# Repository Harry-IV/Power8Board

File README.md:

# Power8Board V1

48V → 12V Power Distribution & Current-Sensing Board for 8 Thrusters

## Overview

Power8Board is a custom power distribution and sensing PCB intended for robotics applications (e.g. ROVs / AUVs) where 6 DoF control is needed from eight thrusters. 

The board converts 48V DC into 5V and 12V rails, distributes power to eight ESCs, and provides per-thruster current measurement and voltage rail monitoring (3.3, 5, 12, 48) over I²C.

---

## Power Architecture

Two [MPQ860-12V72-L48NBMC](https://www.digikey.com/en/products/detail/murata-power-solutions-inc/MPQ860-12V72-L48NBMC/26005878?s=N4IgTCBcDaILYAcCOAOAbABhAXQL5A) 860W power converters are used to step down 48 to 12V with high efficiency. This 12V power is then routed to eight XT30U-M connectors which ESCs can then connect to for power. These were chosen due to having four power pins, allowing for better heat distribution, and for their active current sharing capabilities. With ~1500W (not 1720 due to drop in max wattage output when current sharing), eight standard T200 thrusters can be driven at full power. This 12V can also be used to power other 12V devices using the [MR30 connector](https://www.tme.com/us/en-us/details/mr30pw-m/dc-power-connectors/amass/) on the board. 

Additionally, a [UWS-5/10-Q48N-C](https://www.digikey.com/en/products/detail/murata-power-solutions-inc/UWS-5-10-Q48N-C/3041704?s=N4IgTCBcDaIKoHUDKBaArAegIwAYUEUAWADgDkUBhEAXQF8g) 100W power converter is used to step down 48V to 5V. This 5V is outputted through the MR30 and can be used to power a Raspberry Pi for instance.

---

## Current Sensing

Monitor thruster load and detect abnormal conditions (e.g. over-current):

### Current-Sense Amplifiers
  * [INA240A2](https://www.ti.com/product/INA240) (analog)
  * One per ESC channel
  * 50x amplification value (50V/V gain)
* 0.0033 $\Omega$ shunt resistor placed in series with each 12V output
  * Scale factor: 1 / (SHUNT_VALUE * AMP_FACTOR) = 1 / (0.0033 * 50) = 6.061
  * current = 6.061 * (output of INA240)
* Analog output routed to ADC inputs with RC-filter (680 $\Omega$, 2.2 uF)

### Channel Organization

* Left side: 4 thrusters
* Right side: 4 thrusters
* Each side feeds into its own ADC, an [ADS1015](https://www.ti.com/product/ADS1015) (12-bit, I²C interfacing)
* I²C address:
  * Left: 0x48
  * Right: 0x49

---

## Voltage Sensing

Monitor that voltage rails are within normal bounds.

### Power Rails

| Rail  | Purpose                    |
| ----- | -------------------------- |
| 48 V  | Main input power           |
| 12 V  | ESC & thruster power       |
| 5 V   | Miscellaneous              |
| 3.3 V | ADCs, current sensors, I²C |

### ADC

* [ADS1015](https://www.ti.com/product/ADS1015) (12-bit, I²C interfacing)
  * Used for measuring the voltages
  * Address: 0x4A

### Voltage Dividers

### Scalar Values
  * 48V: (470+25)/25 = 19.8
  * 12V: (470+110)/110 = 5.273
  * 5V: (470+470)/470 = 2
  * 3.3V: (470+470)/470 = 2

Multiply these values read from the ADC by these scalars respectively to find their true voltages.

---

## LED Indicators

| Rail  | Color                      |
| ----- | -------------------------- |
| 48 V  | Green                      |
| 12 V  | Yellow                     |
| 5 V   | Red                        |
| 3.3 V | Amber                      |

---

## PCB Layout

### 6-layer stackup

| Layer | Type                      |
| ----- | ------------------------- |
| 1     | Signal                    |
| 2     | Ground                    |
| 3     | Signal - Power (3.3V)     |
| 4     | Power (12V & 48V)         |
| 5     | Ground                    |
| 6     | Signal                    |

### Design notes

* Nearly all analog traces are routed on layer 3 to reduce effects of digital noise.
* Copper pours help with thermal dissipation.
* Via-in-pad is used to condense routing. It's also a standard option for 6-layer boards when ordering with JLCPCB.
* Ground on layer 2 & 5 provides low-impedance return path and reduce EMI.
* Power converters connect from the backside. 

---

## Ordering

To order, navigate to Power8Board V1/Export. Use Power8Board V1.zip for ordering the PCB and Power8Board V1 Stencil.zip for ordering a stencil (very helpful for soldering). Here are the options I chose when ordering from JLCPCB:

For ordering the components, navigate to Power8Board V1/bom and click on ibom.html. This BOM is interactive, making it great for ordering and knowing where components go while soldering. **Note that this does not include all components for making the board.** This is because pin receptacles are soldered onto the pads for all power converters. Here are the two types of pin receptacles used on the board:

Pin #1: https://www.digikey.com/en/products/detail/mill-max-manufacturing-corp/0372-0-15-15-13-27-10-0/433860

Pin #2: https://www.digikey.com/en/products/detail/mill-max-manufacturing-corp/0312-0-15-15-34-27-10-0/433567

Pin #1 is used on pads 4, 5, 7, and 8 on both 48V-12V converters and on pads 4 and 8 on the 48V-5V converter (10 in total)

Pin #2 is used on pads 1, 2, and 3 on both 48V-12V converters and on pads 1, 2, 3, 5, 6, and 7 on the 48V-5V converter (12 in total)

---

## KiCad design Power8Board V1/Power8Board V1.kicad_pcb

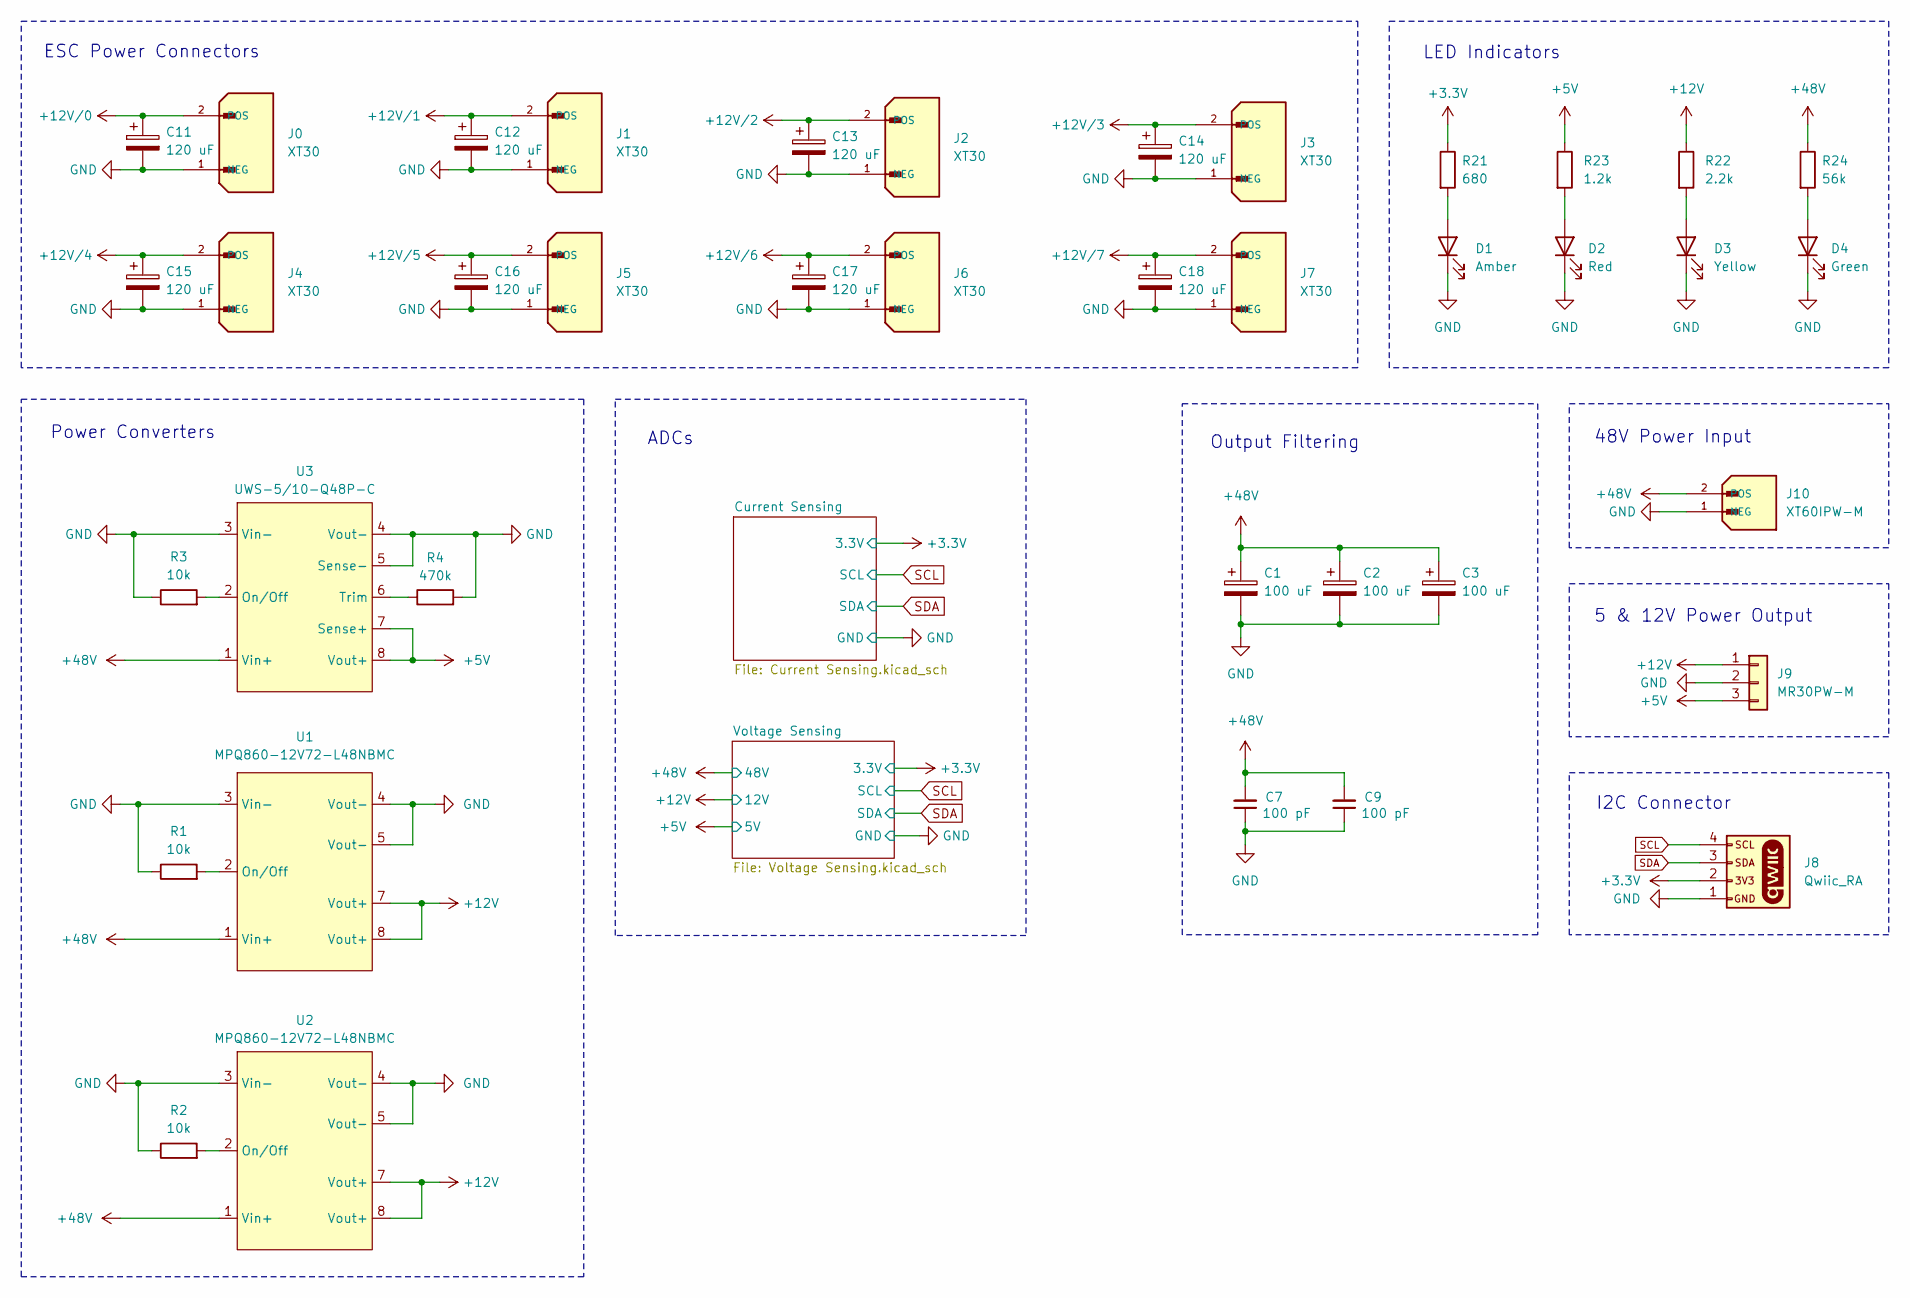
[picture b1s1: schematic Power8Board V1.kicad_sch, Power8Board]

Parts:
C1, C2, C3: 100 uF; CAP_AVG-8x12_ILC; Part # 107AVG063MFBJ
C7, C9: 100 pF; CAPC2012X140N; Part # KGQ21HCG2A101JT
C11, C12, C13, C14, C15, C16, C17, C18: 120 uF; PCAP_SVP_C6_PAN-M; Part # 20SVPF120M
D1: Amber; WL-SMCW_0805; Part # 150080AS75000
D2: Red; WL-SMCW_0805; Part # 150080RS75000
D3: Yellow; WL-SMCW_0805; Part # 150080YS75000
D4: Green; WL-SMCW_0805; Part # 150080GS75000
J0, J1, J2, J3, J4, J5, J6, J7: XT30; AMASS_XT30U-M_1x02_P5.0mm_Vertical; Part # XT30U-M
J8: Qwiic_RA; QWIIC Connector RA; Part # SM04B-SRSS-TB
J9: MR30PW-M; AMASS_MR30PW-M_1x03_P3.50mm_Horizontal; Part # MR30PW-M
J10: XT60IPW-M; AMASS_XT60IPW-M_1x03_P7.20mm_Horizontal; Part # XT60IPW-M
R1, R2, R3: 10k; R_0805_2012Metric; Part # CRGCQ0805F10K
R4: 470k; R_0805_2012Metric; Part # CRGCQ0805F470K
R21: 680; R_0805_2012Metric; Part # CRGCQ0805F680R
R22: 2.2k; R_0805_2012Metric; Part # CRGCQ0805F2K2
R23: 1.2k; R_0805_2012Metric; Part # CRGCQ0805F1K2
R24: 56k; R_0805_2012Metric; Part # CRGCQ0805F56K
U1, U2: MPQ860-12V72-L48NBMC; Part # MPQ860-12V72-L48NBMC
U3: UWS-5_10-Q48; Part # UWS-5/10-Q48P-C

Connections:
+3.3V: J8.2, R21.1; also elsewhere on the board
+5V: J9.3, R23.1, U3.7 (Sense+), U3.8 (Vout+); also elsewhere on the board
+12V: J9.1, R22.1, U1.7 (Vout+), U1.8 (Vout+), U2.7 (Vout+), U2.8 (Vout+); also elsewhere on the board
+12V/0: C11.1, J0.2 (POS); also elsewhere on the board
+12V/1: C12.1, J1.2 (POS); also elsewhere on the board
+12V/2: C13.1, J2.2 (POS); also elsewhere on the board
+12V/3: C14.1, J3.2 (POS); also elsewhere on the board
+12V/4: C15.1, J4.2 (POS); also elsewhere on the board
+12V/5: C16.1, J5.2 (POS); also elsewhere on the board
+12V/6: C17.1, J6.2 (POS); also elsewhere on the board
+12V/7: C18.1, J7.2 (POS); also elsewhere on the board
+48V: C1.1, C2.1, C3.1, C7.2, C9.2, J10.2 (POS), R24.1, U1.1 (Vin+), U2.1 (Vin+), U3.1 (Vin+); also elsewhere on the board
GND: C1.2, C2.2, C3.2, C7.1, C9.1, C11.2, C12.2, C13.2, C14.2, C15.2, C16.2, C17.2, C18.2, D1.1 (K), D2.1 (K), D3.1 (K), D4.1 (K), J0.1 (NEG), J1.1 (NEG), J2.1 (NEG), J3.1 (NEG), J4.1 (NEG), J5.1 (NEG), J6.1 (NEG), J7.1 (NEG), J8.1, J9.2, J10.1 (NEG), R1.1, R2.1, R3.1, R4.2, U1.3 (Vin-), U1.4 (Vout-), U1.5 (Vout-), U2.3 (Vin-), U2.4 (Vout-), U2.5 (Vout-), U3.3 (Vin-), U3.4 (Vout-), U3.5 (Sense-); also elsewhere on the board
unnamed: D1.2 (A), R21.2
unnamed: D2.2 (A), R23.2
unnamed: D3.2 (A), R22.2
unnamed: D4.2 (A), R24.2
unnamed: R1.2, U1.2 (On/Off)
unnamed: R2.2, U2.2 (On/Off)
unnamed: R3.2, U3.2 (On/Off)
unnamed: R4.1, U3.6 (Trim)
SCL: J8.4; also elsewhere on the board
SDA: J8.3; also elsewhere on the board

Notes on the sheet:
I2C Connector
LED Indicators
48V Power Input
ADCs
Power Converters
Output Filtering
5 & 12V Power Output
ESC Power Connectors

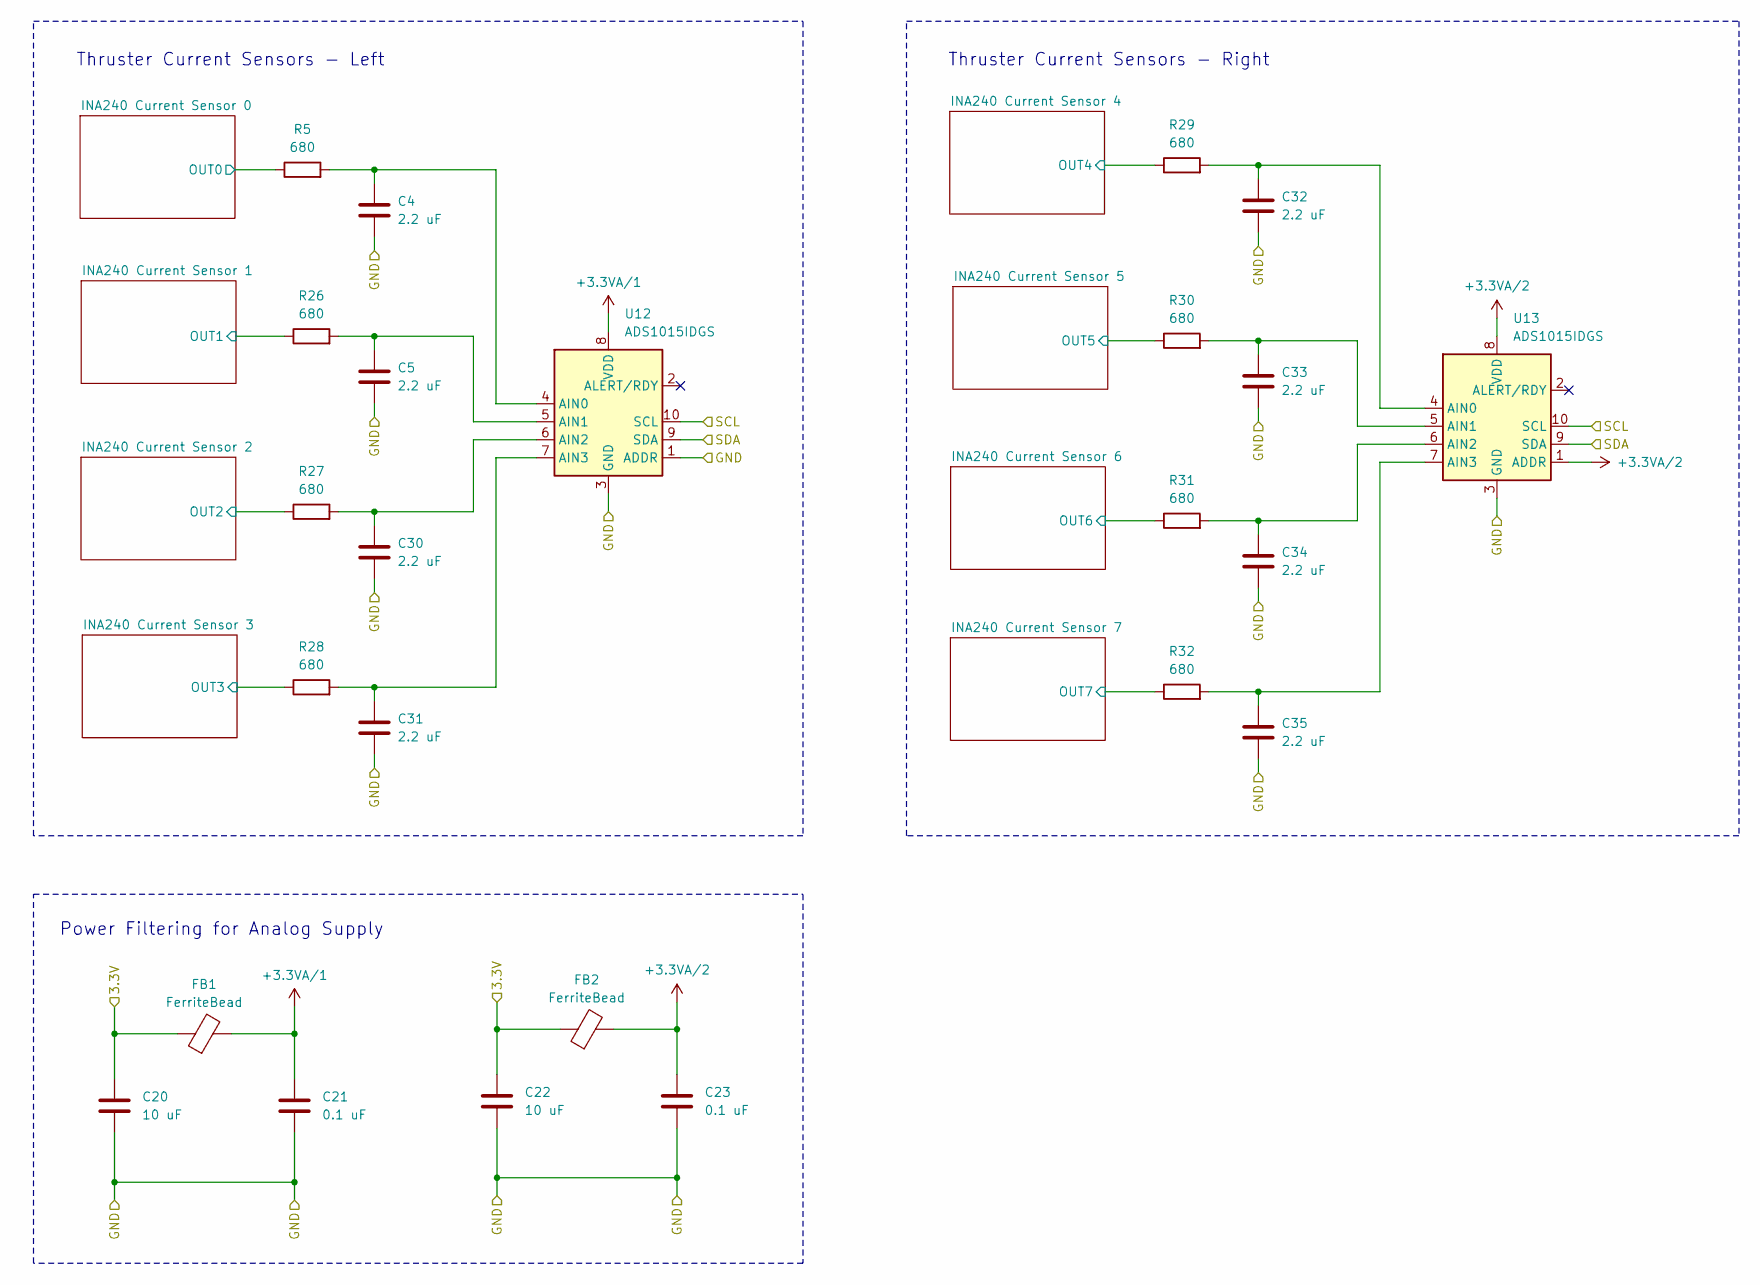
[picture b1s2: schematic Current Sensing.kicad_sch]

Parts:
C4, C5, C30, C31, C32, C33, C34, C35: 2.2 uF; C_0603_1608Metric; Part # GRM188Z71E225KE43D
C20, C22: 10 uF; C_0603_1608Metric; Part # GRM188R61E106KA73D
C21, C23: 0.1 uF; C_0603_1608Metric; Part # C0603C104K5RACTU
FB1, FB2: FerriteBead; 0603 Ferrite Bead; Part # BLM18KG102SZ1D
R5, R26, R27, R28, R29, R30, R31, R32: 680; R_0603_1608Metric; Part # CRGCQ0603F680R
U12, U13: ADS1015IDGS; TSSOP-10_3x3mm_P0.5mm; Part # ADS1015IDGSR

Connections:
+3.3V: C20.1, C22.1, FB1.1, FB2.1; also elsewhere on the board
+3.3VA/1: C21.1, FB1.2, U12.8 (VDD)
+3.3VA/2: C23.1, FB2.2, U13.1 (ADDR), U13.8 (VDD)
/Current Sensing/INA240 Current Sensor 0/OUT0: R5.1; also elsewhere on the board
/Current Sensing/INA240 Current Sensor 1/OUT1: R26.1; also elsewhere on the board
/Current Sensing/INA240 Current Sensor 2/OUT2: R27.1; also elsewhere on the board
/Current Sensing/INA240 Current Sensor 3/OUT3: R28.1; also elsewhere on the board
/Current Sensing/INA240 Current Sensor 4/OUT4: R29.1; also elsewhere on the board
/Current Sensing/INA240 Current Sensor 5/OUT5: R30.1; also elsewhere on the board
/Current Sensing/INA240 Current Sensor 6/OUT6: R31.1; also elsewhere on the board
/Current Sensing/INA240 Current Sensor 7/OUT7: R32.1; also elsewhere on the board
GND: C4.2, C5.2, C20.2, C21.2, C22.2, C23.2, C30.2, C31.2, C32.2, C33.2, C34.2, C35.2, U12.1 (ADDR), U12.3 (GND), U13.3 (GND); also elsewhere on the board
unnamed: C4.1, R5.2, U12.4 (AIN0)
unnamed: C5.1, R26.2, U12.5 (AIN1)
unnamed: C30.1, R27.2, U12.6 (AIN2)
unnamed: C31.1, R28.2, U12.7 (AIN3)
unnamed: C32.1, R29.2, U13.4 (AIN0)
unnamed: C33.1, R30.2, U13.5 (AIN1)
unnamed: C34.1, R31.2, U13.6 (AIN2)
unnamed: C35.1, R32.2, U13.7 (AIN3)
SCL: U12.10 (SCL), U13.10 (SCL); also elsewhere on the board
SDA: U12.9 (SDA), U13.9 (SDA); also elsewhere on the board

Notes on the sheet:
Thruster Current Sensors - Right
Power Filtering for Analog Supply
Thruster Current Sensors - Left

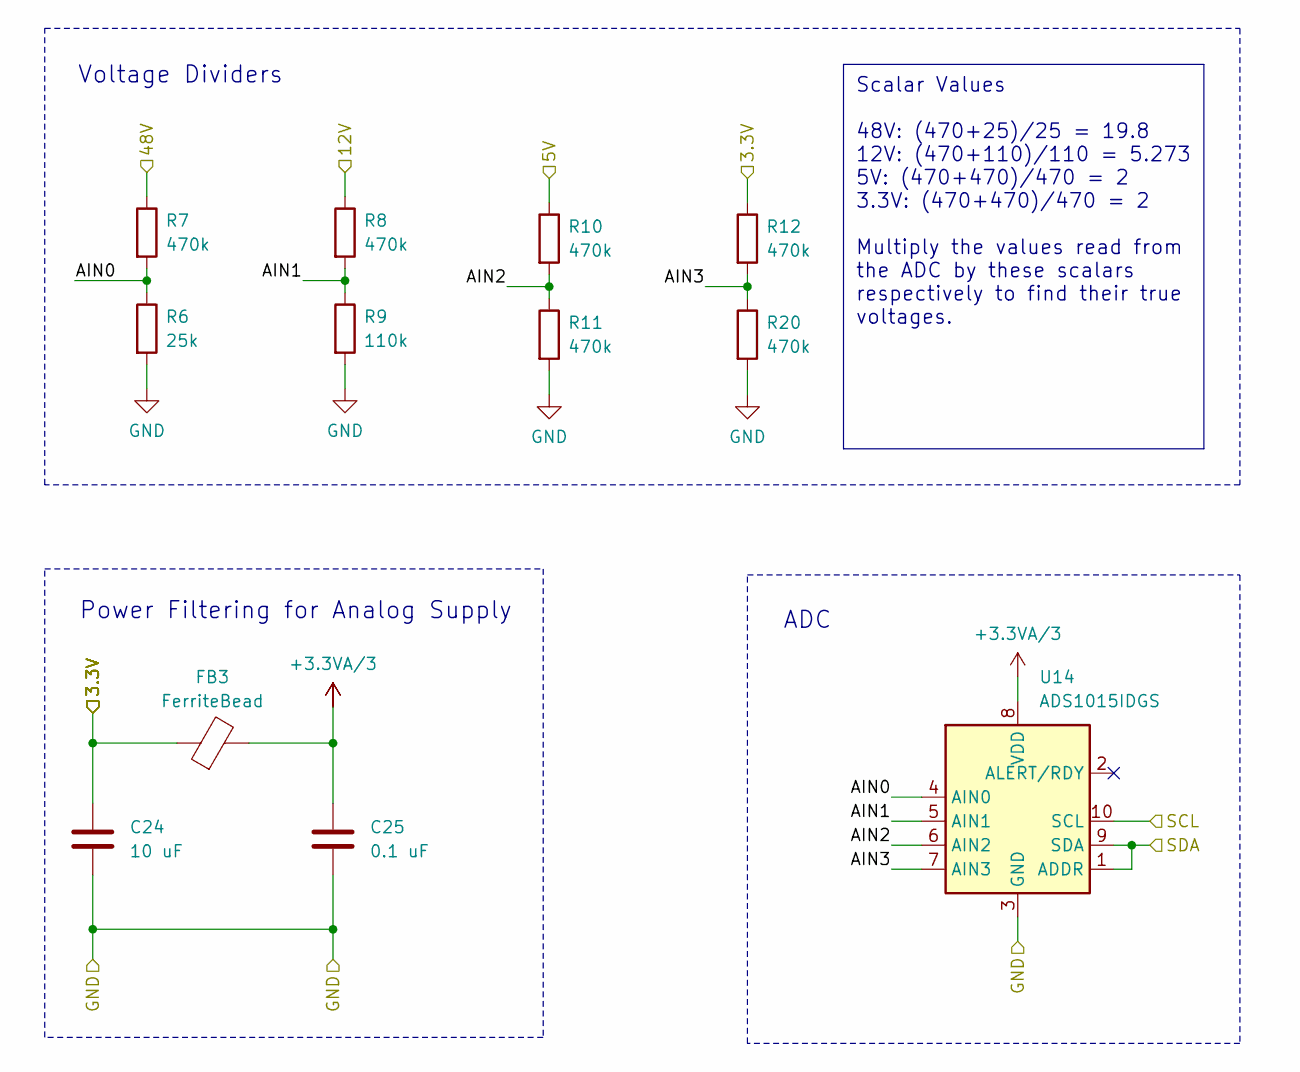
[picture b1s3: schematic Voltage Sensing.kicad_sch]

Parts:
C24: 10 uF; C_0805_2012Metric; Part # GRT21BC71E106KE13L
C25: 0.1 uF; C_0805_2012Metric; Part # C0805C104J5RACAUTO
FB3: FerriteBead; BEADC2012X105N; Part # MPZ2012S102ATD25
R6: 25k; R_0805_2012Metric; Part # CPF-A-0805B25KE
R7, R8, R10, R11, R12, R20: 470k; RES_TNPW0805_VIS; Part # TNPW0805470KBEEA
R9: 110k; R_0805_2012Metric; Part # RQ73C2A110KBTDF
U14: ADS1015IDGS; TSSOP-10_3x3mm_P0.5mm; Part # ADS1015IDGSR

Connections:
+3.3V: C24.1, FB3.1, R12.1; also elsewhere on the board
+3.3VA/3: C25.1, FB3.2, U14.8 (VDD)
+5V: R10.1; also elsewhere on the board
+12V: R8.1; also elsewhere on the board
+48V: R7.1; also elsewhere on the board
/Voltage Sensing/AIN0: R6.1, R7.2, U14.4 (AIN0)
/Voltage Sensing/AIN1: R8.2, R9.1, U14.5 (AIN1)
/Voltage Sensing/AIN2: R10.2, R11.1, U14.6 (AIN2)
/Voltage Sensing/AIN3: R12.2, R20.1, U14.7 (AIN3)
GND: C24.2, C25.2, R6.2, R9.2, R11.2, R20.2, U14.3 (GND); also elsewhere on the board
SCL: U14.10 (SCL); also elsewhere on the board
SDA: U14.1 (ADDR), U14.9 (SDA); also elsewhere on the board

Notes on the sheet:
Scalar Values 48V: (470+25)/25 = 19.8 12V: (470+110)/110 = 5.273 5V: (470+470)/470 = 2 3.3V: (470+470)/470 = 2 Multiply the values read from the ADC by these scalars respectively to find their true voltages.
ADC
Power Filtering for Analog Supply
Voltage Dividers

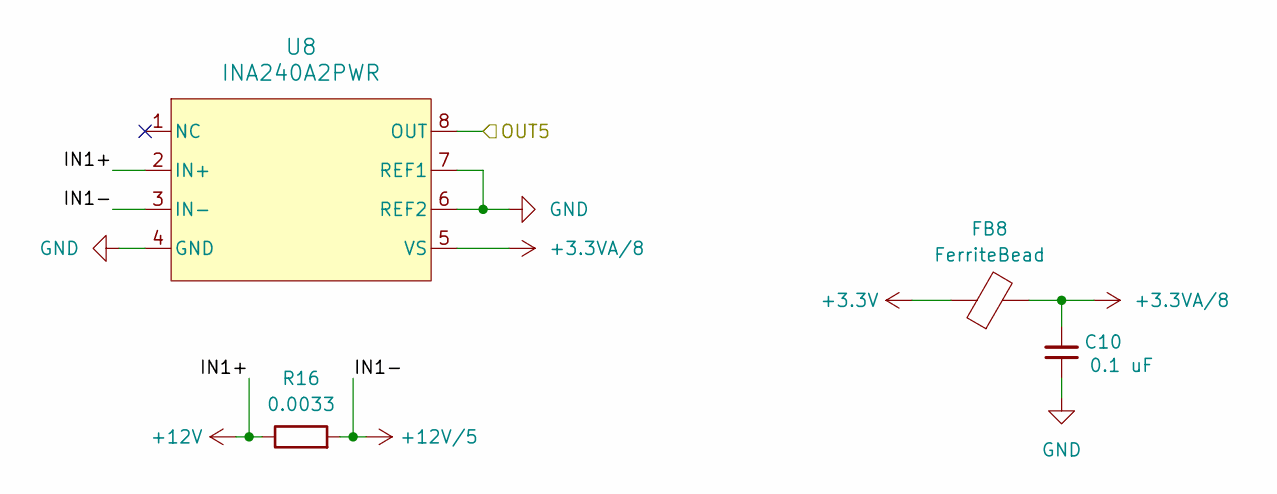
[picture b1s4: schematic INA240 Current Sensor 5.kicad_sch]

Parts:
C10: 0.1 uF; CAPC2012X140N; Part # C0805C104J5RACAUTO
FB8: FerriteBead; BEADC2012X105N; Part # MPZ2012S102ATD25
R16: 0.0033; RES_VISHAY_WSLP2512_A_VIS; Part # WSLP25123L300DEA
U8: INA240A2PWR; PW0008A_M; Part # INA240A2PWR

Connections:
+3.3V: FB8.1; also elsewhere on the board
+3.3VA/8: C10.2, FB8.2, U8.5 (VS)
+12V: R16.1, U8.2 (IN+); also elsewhere on the board
+12V/5: R16.2, U8.3 (IN-); also elsewhere on the board
/Current Sensing/INA240 Current Sensor 5/OUT5: U8.8 (OUT); also elsewhere on the board
GND: C10.1, U8.4 (GND), U8.6 (REF2), U8.7 (REF1); also elsewhere on the board

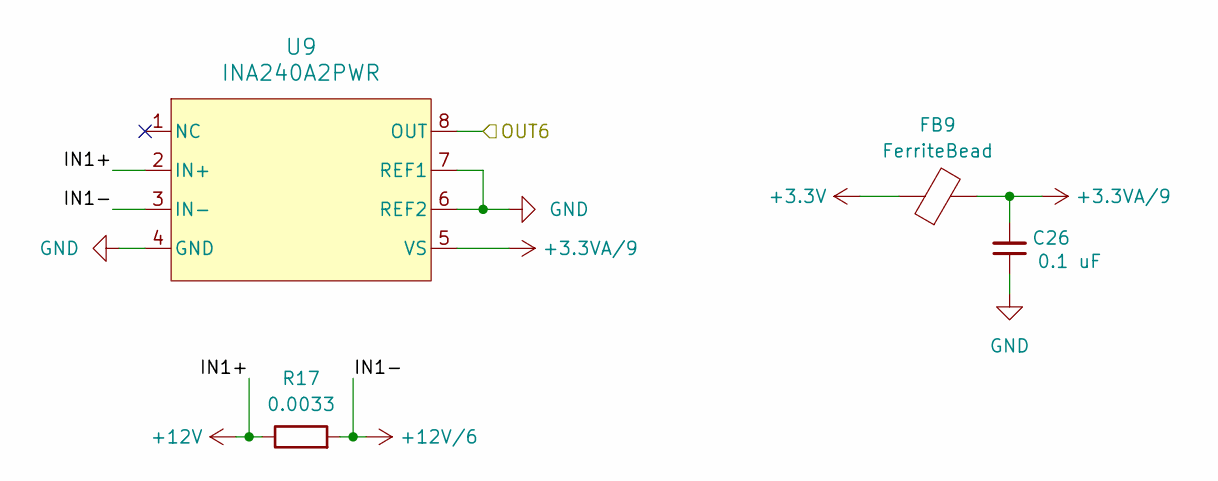
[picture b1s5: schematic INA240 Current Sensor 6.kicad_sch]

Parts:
C26: 0.1 uF; CAPC2012X140N; Part # C0805C104J5RACAUTO
FB9: FerriteBead; BEADC2012X105N; Part # MPZ2012S102ATD25
R17: 0.0033; RES_VISHAY_WSLP2512_A_VIS; Part # WSLP25123L300DEA
U9: INA240A2PWR; PW0008A_M; Part # INA240A2PWR

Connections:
+3.3V: FB9.1; also elsewhere on the board
+3.3VA/9: C26.2, FB9.2, U9.5 (VS)
+12V: R17.1, U9.2 (IN+); also elsewhere on the board
+12V/6: R17.2, U9.3 (IN-); also elsewhere on the board
/Current Sensing/INA240 Current Sensor 6/OUT6: U9.8 (OUT); also elsewhere on the board
GND: C26.1, U9.4 (GND), U9.6 (REF2), U9.7 (REF1); also elsewhere on the board

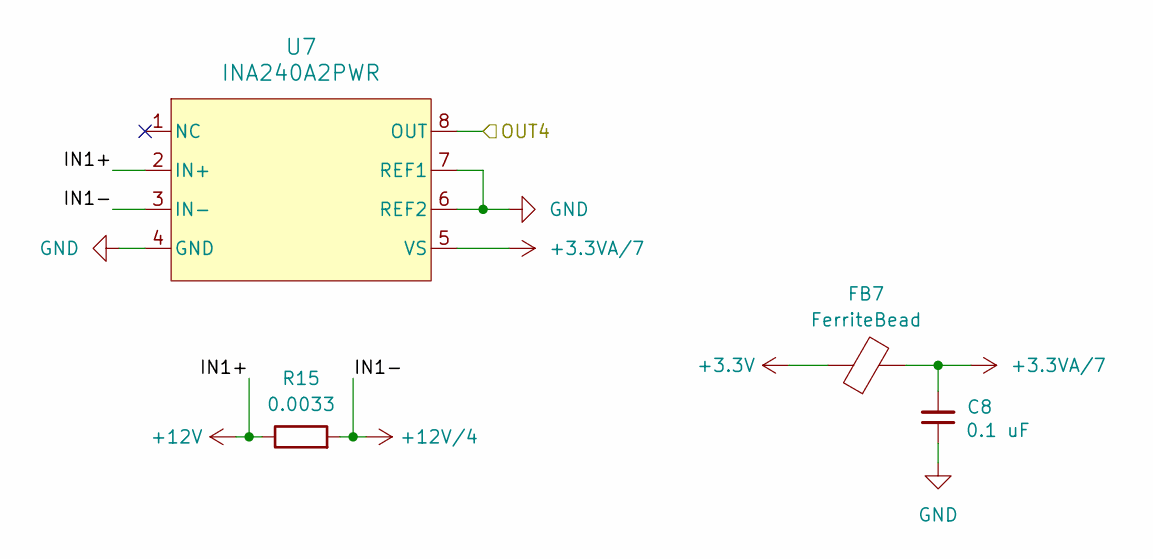
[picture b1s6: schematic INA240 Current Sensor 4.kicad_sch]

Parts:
C8: 0.1 uF; CAPC2012X140N; Part # C0805C104J5RACAUTO
FB7: FerriteBead; BEADC2012X105N; Part # MPZ2012S102ATD25
R15: 0.0033; RES_VISHAY_WSLP2512_A_VIS; Part # WSLP25123L300DEA
U7: INA240A2PWR; PW0008A_M; Part # INA240A2PWR

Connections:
+3.3V: FB7.1; also elsewhere on the board
+3.3VA/7: C8.2, FB7.2, U7.5 (VS)
+12V: R15.1, U7.2 (IN+); also elsewhere on the board
+12V/4: R15.2, U7.3 (IN-); also elsewhere on the board
/Current Sensing/INA240 Current Sensor 4/OUT4: U7.8 (OUT); also elsewhere on the board
GND: C8.1, U7.4 (GND), U7.6 (REF2), U7.7 (REF1); also elsewhere on the board

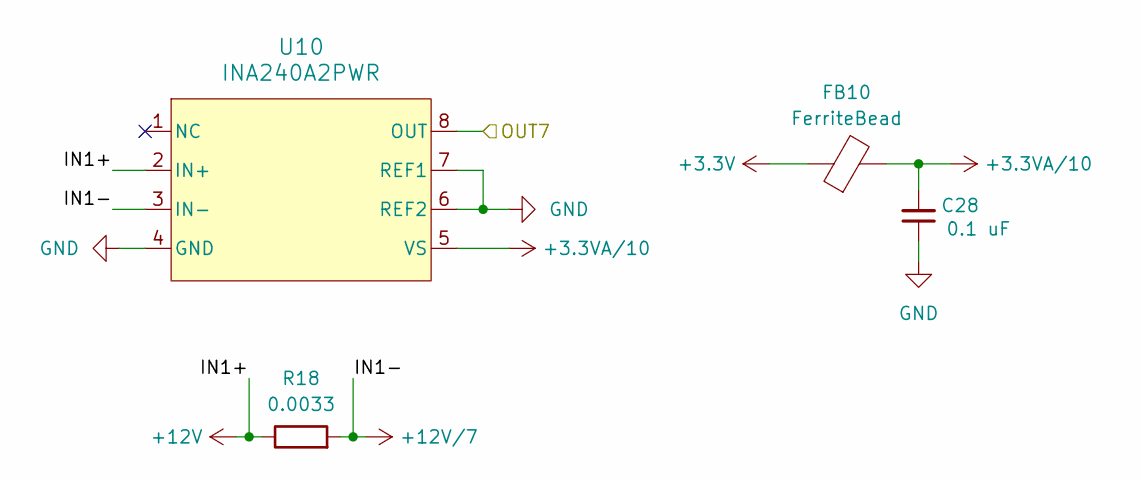
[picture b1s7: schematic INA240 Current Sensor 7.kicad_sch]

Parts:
C28: 0.1 uF; CAPC2012X140N; Part # C0805C104J5RACAUTO
FB10: FerriteBead; BEADC2012X105N; Part # MPZ2012S102ATD25
R18: 0.0033; RES_VISHAY_WSLP2512_A_VIS; Part # WSLP25123L300DEA
U10: INA240A2PWR; PW0008A_M; Part # INA240A2PWR

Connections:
+3.3V: FB10.1; also elsewhere on the board
+3.3VA/10: C28.2, FB10.2, U10.5 (VS)
+12V: R18.1, U10.2 (IN+); also elsewhere on the board
+12V/7: R18.2, U10.3 (IN-); also elsewhere on the board
/Current Sensing/INA240 Current Sensor 7/OUT7: U10.8 (OUT); also elsewhere on the board
GND: C28.1, U10.4 (GND), U10.6 (REF2), U10.7 (REF1); also elsewhere on the board

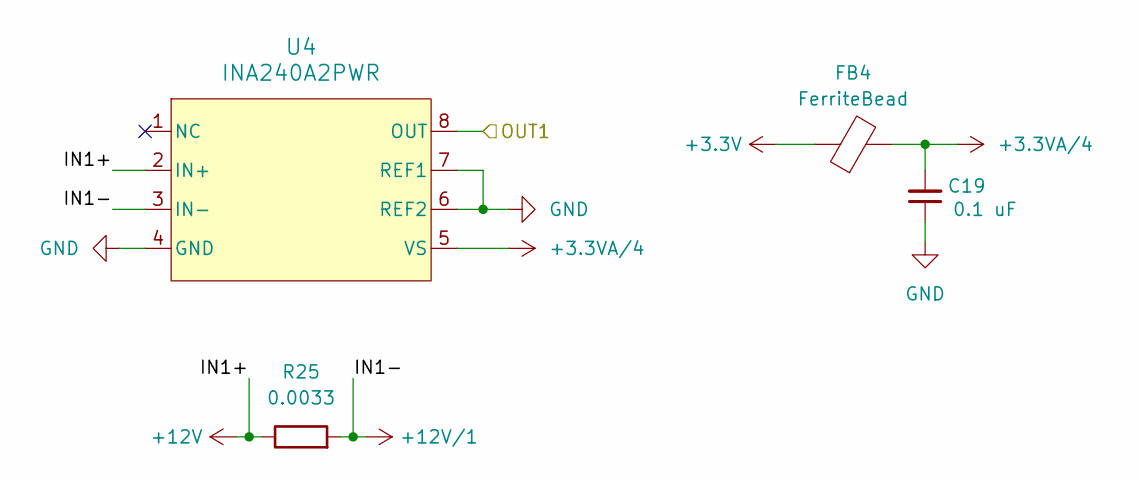
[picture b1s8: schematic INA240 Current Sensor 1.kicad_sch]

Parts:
C19: 0.1 uF; CAPC2012X140N; Part # C0805C104J5RACAUTO
FB4: FerriteBead; BEADC2012X105N; Part # MPZ2012S102ATD25
R25: 0.0033; RES_VISHAY_WSLP2512_A_VIS; Part # WSLP25123L300DEA
U4: INA240A2PWR; PW0008A_M; Part # INA240A2PWR

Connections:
+3.3V: FB4.1; also elsewhere on the board
+3.3VA/4: C19.2, FB4.2, U4.5 (VS)
+12V: R25.1, U4.2 (IN+); also elsewhere on the board
+12V/1: R25.2, U4.3 (IN-); also elsewhere on the board
/Current Sensing/INA240 Current Sensor 1/OUT1: U4.8 (OUT); also elsewhere on the board
GND: C19.1, U4.4 (GND), U4.6 (REF2), U4.7 (REF1); also elsewhere on the board

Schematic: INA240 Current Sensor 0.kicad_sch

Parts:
C29: 0.1 uF; CAPC2012X140N; Part # C0805C104J5RACAUTO
FB11: FerriteBead; BEADC2012X105N; Part # MPZ2012S102ATD25
R19: 0.0033; RES_VISHAY_WSLP2512_A_VIS; Part # WSLP25123L300DEA
U11: INA240A2PWR; PW0008A_M; Part # INA240A2PWR

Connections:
+3.3V: FB11.1; also elsewhere on the board
+3.3VA/11: C29.2, FB11.2, U11.5 (VS)
+12V: R19.1, U11.2 (IN+); also elsewhere on the board
+12V/0: R19.2, U11.3 (IN-); also elsewhere on the board
/Current Sensing/INA240 Current Sensor 0/OUT0: U11.8 (OUT); also elsewhere on the board
GND: C29.1, U11.4 (GND), U11.6 (REF2), U11.7 (REF1); also elsewhere on the board

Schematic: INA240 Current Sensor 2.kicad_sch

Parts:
C27: 0.1 uF; CAPC2012X140N; Part # C0805C104J5RACAUTO
FB5: FerriteBead; BEADC2012X105N; Part # MPZ2012S102ATD25
R13: 0.0033; RES_VISHAY_WSLP2512_A_VIS; Part # WSLP25123L300DEA
U5: INA240A2PWR; PW0008A_M; Part # INA240A2PWR

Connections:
+3.3V: FB5.1; also elsewhere on the board
+3.3VA/5: C27.2, FB5.2, U5.5 (VS)
+12V: R13.1, U5.2 (IN+); also elsewhere on the board
+12V/2: R13.2, U5.3 (IN-); also elsewhere on the board
/Current Sensing/INA240 Current Sensor 2/OUT2: U5.8 (OUT); also elsewhere on the board
GND: C27.1, U5.4 (GND), U5.6 (REF2), U5.7 (REF1); also elsewhere on the board

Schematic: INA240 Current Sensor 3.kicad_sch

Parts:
C6: 0.1 uF; CAPC2012X140N; Part # C0805C104J5RACAUTO
FB6: FerriteBead; BEADC2012X105N; Part # MPZ2012S102ATD25
R14: 0.0033; RES_VISHAY_WSLP2512_A_VIS; Part # WSLP25123L300DEA
U6: INA240A2PWR; PW0008A_M; Part # INA240A2PWR

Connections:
+3.3V: FB6.1; also elsewhere on the board
+3.3VA/6: C6.2, FB6.2, U6.5 (VS)
+12V: R14.1, U6.2 (IN+); also elsewhere on the board
+12V/3: R14.2, U6.3 (IN-); also elsewhere on the board
/Current Sensing/INA240 Current Sensor 3/OUT3: U6.8 (OUT); also elsewhere on the board
GND: C6.1, U6.4 (GND), U6.6 (REF2), U6.7 (REF1); also elsewhere on the board

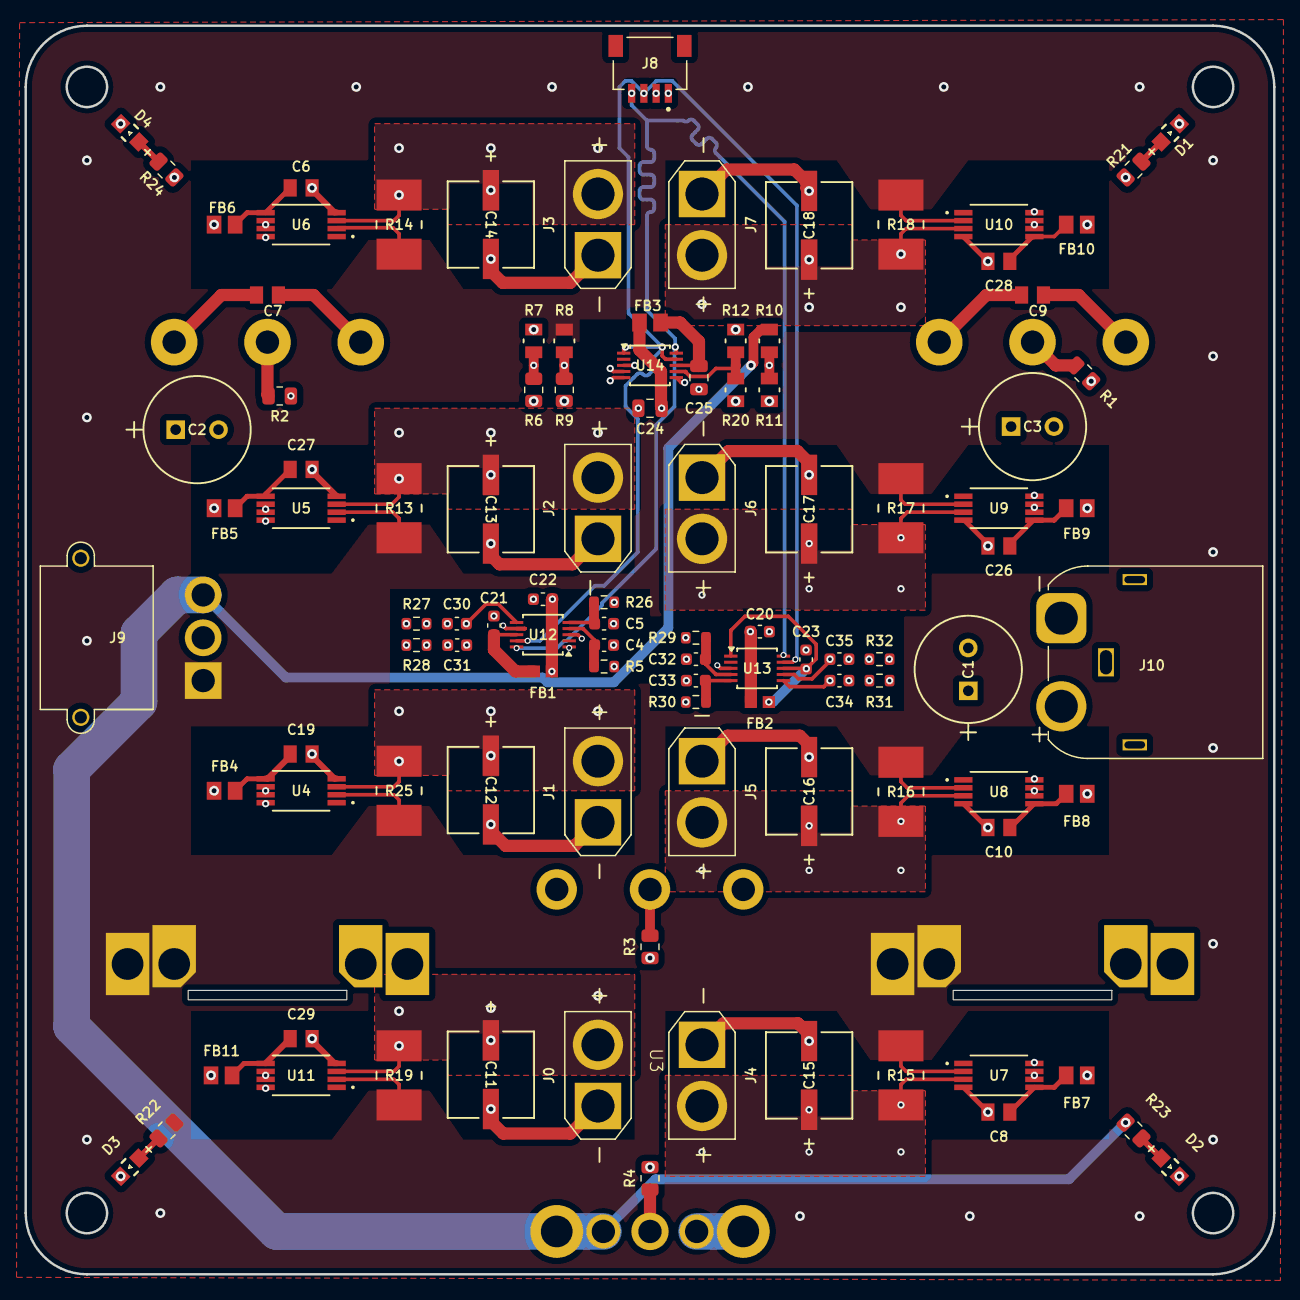
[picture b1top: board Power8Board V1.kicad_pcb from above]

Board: 6 copper layers, 102.0 x 102.0 mm, 107 parts (0 on the bottom side), 54 nets.

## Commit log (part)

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2025-08-12 Progress up to 8/11/2025.
2025-08-26 Added voltage and current sensing.
2025-08-28 Added power indicator LEDs.
2025-08-29 Design before laying out.
2025-08-30 Beginning to layout.
2025-09-01 There is a general layout.
2025-09-04 Laid out components
2025-09-05 Laying out 9/5.
2025-09-06 About half a side is done.
2025-09-08 Switched out input capacitors.
2025-09-20 Added 0603 components and RC filters.
2025-09-23 9/22 Progress
2025-09-23 9/23 Progress
2025-09-24 DRC sorted out.
2025-09-25 PCB before BOM creation.
2025-09-26 Ordered PCB.
2025-09-29 Includes most recent BOM.
2025-12-25 Added boxes in schematic for organization.
2025-12-25 Moved current sensor schematics to Current Sensor folder.
2025-12-25 Added non KiCad standard components in Components folder.
2025-12-25 Fixed .gitignore
2025-12-25 Removed KiCad generated files and backups from tracking.
2025-12-26 Added README
    Added detailed documentation for the Power8Board V1, including power architecture, current sensing, voltage sensing, LED indicators, PCB layout, and ordering instructions.
2025-12-27 Fix wording in design notes.
2025-12-27 Add GNU GPL v3 license
    Added the GNU General Public License version 3 to the project.
